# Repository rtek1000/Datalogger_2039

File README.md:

# Datalogger 2039
- This is an 8-channel logger for collecting temperature data (431 160 readings).
- - Data export via USB Flash Drive (Pendrive).
- - Digital sensor.
- Project started in Jan/2019.
- - Note: Work in progress, just demonstrative, not (fully) functional, sorry.
- - If you are using a browser on your smartphone, use the landscape screen to read more characters in the file names.
- - - (These files have already been cited elsewhere, and changing the name of the folders causes corruption of the references)

-------

## Features:
- 12-bit temperature sensor [DS18B20 from -55°C to +125°C (-67°F to +257°F)]
- - Needs two cycles to reset fault (Cycle 1: Start converting; Cycle 2: Read)
- 16-bit temperature sensor [TMP117 from -55°C to 150°C and from 0°C to 85°C for letter M code)]
- Short circuit protection for sensors (power and data line).
- Short-circuit protection for the USB ports (power line).
- 56 characters channel label.
- Special character supported for channel label (À/Á/Ã/Â/Ä).
- Channel label Ctrl+C/Ctrl+V (copy/paste) supported.
- 53 895 readings per channel (37 days, 10 hours and 15 minutes @ 1 minute interval).
- Control access to settings and data export via password.
- Export data via USB Flash Drive (Pendrive) (*.dat file).
- - Before removing the USB disk It is recommended to exit the Export screen to completely disable the USB port.
- - Need to format the USB disk in FAT (FAT32, LBA; exFAT may be faster), or it will give an error.
- - Output file with part of the data encoded in Base64. Need to decode the data to import into a spreadsheet, see the File Converter App.
- - Formatting USB flash drive on [Android](https://support-en.wd.com/app/answers/detailweb/a_id/40101/~/format-a-usb-drive-or-memory-card-using-android) did not cause error (tested on Motorola Smartphone and Android version 10).
- - Quick formatting may cause an error if the previous partition is not FAT, in this case use full formatting.
- USB Flash Drive (Pendrive) format function (Be careful, all files will be lost).
- - Some USB disks may not be recognized correctly on Android smartphones when using exFAT.
- Edit parameters via USB keyboard.
- - Keyboard may take a few seconds to recognize.
- - Support to [Wireless Mini Keyboard with Touchpad built in](https://github.com/rtek1000/Datalogger_2039/blob/main/Hardware/Wireless%20Mini%20Keyboard/Mini_Keyboard_Colors.jpg) ([Tested with PT-BR layout](https://github.com/rtek1000/Datalogger_2039/tree/main/Hardware/Wireless%20Mini%20Keyboard)).
- Cabinet tilt monitoring.
- Battery and charger voltage monitoring.
- Battery polarity reversal protection (In case the Datalogger 2039 is using two batteries, it is not recommended to reverse any of them, or it may damage the battery).
- Monitoring of data in colored graph.
- Can save Screenshot to USB flash drive (PrintScreen key).
- Multiple languages (English, Portuguese and Spanish).
- [Integrated firmware integrity check (CRC)](https://community.st.com/t5/security-mcu/how-to-use-hal-crc-accumulate-bufferlength-does-not-accept-the/td-p/252363).
- Energy saving for prolonged battery charge and durability of the LCD backlight.
- - Microcontroller operates in two modes, low power at only 40MHz clock and normal power at 168MHz clock.
- - The display is activated only when the microcontroller is clocked at 168MHz.
- - The display backlight has 3 operating states: high brightness, low brightness and off.
- - When the sensor is read, a conversion interval of 750ms is required (DS18B20), during which time the microcontroller sleeps.
- Temperature offset. On the sensors screen, press the number between 1 and 8 to open the offset adjustment screen.

## Software:
- Firmware for STM32F407VGT6 microcontroller:
- - STM32CubeIDE - C language project (HAL).
- File Converter:
- -  ̶B̶4̶J̶ ̶-̶ ̶B̶a̶s̶i̶c̶ ̶l̶a̶n̶g̶u̶a̶g̶e̶ ̶p̶r̶o̶j̶e̶c̶t̶ ̶(̶J̶a̶v̶a̶ ̶-̶ ̶c̶r̶o̶s̶s̶ ̶p̶l̶a̶t̶f̶o̶r̶m̶)̶.̶
- - Dot Net 4.0 - [SharpDevelop 4.4.1](https://sourceforge.net/projects/sharpdevelop/files/SharpDevelop%204.x/4.4/)

## Hardware:
- STM32F407VGT6: Dual USB port microcontroller.
- DS18B20: OneWire digital temperature sensor (±0.5°C Accuracy from -10°C to +85°C).
- TMP117: I2C digital temperature sensor (±0.1°C; 16 bits).
- TCA9548A: 8CH I2C Multiplexer.
- CD74HC595: Port expansion (8-Bit Serial-In, Parallel-Out Shift)
- ILI9341: SPI TFT LCD 2.4 inch.
- W25Q64: SPI flash memory (64M-bit).
- DS3231: I2C extremely accurate real time clock - RTC.
- - CR2032: Lithium 3.0V battery backup.
- MPU6050: I2C accelerometer (ACC).
- USBLC6-2: ESD protection.
- STMPS2141: Enhanced single channel power switch (500mA continuous current)
- 18650: Li-ion 3.7V battery backup.
- TP4056: Battery charger.
- MCP1700: 1.6 µA Quiescent Current (IQ) Linear voltage regulator.
- LMR14020: High efficiency 2.2 MHz 2A Step-Down Converter (40V, 40µA IQ).
- MT3608: High Efficiency 1.2MHz 2A Step Up Converter (Up to 28V)
- LAN8720: High-Performance 10/100 Ethernet (For future connectivity expansion).
- 12V DC charger (9V~24V x 2A)
- Multi-functional button:
- - For manual activation when in economy mode
- - To force restart of the USB port (keyboard)
- - To force restart the microcontroller

Note:
- Series resistor on the USB line must be removed (cables must be shorter than 5 meters) see video:
- - [STM32 USB training - 07 STM32 USB hardware design]
- - https://www.youtube.com/watch?v=vwlXUOY7KY0&list=PLnMKNibPkDnFFRBVD206EfnnHhQZI4Hxa&index=7

- Calibration?
- - https://thecavepearlproject.org/2016/03/05/ds18b20-calibration-we-finally-nailed-it/

Note: If the pins PA13 (SWDIO) and PA14 (SWCLK) are used (configured for another option other than the default state) it may prevent the ST-Link from working, to solve this problem, keep the BOOT0 (pin 94) in logical state high (3.3V) before energizing (reset the microcontroller). To not need to manually change the BOOT0 pin, keep the pins PA13 (SWDIO) and PA14 (SWCLK) unused, it also cannot be configured as input.

-------

#### ToDo
- Add factory reset (W25Q64 chip erase).
- Add offset adjustment lock if sensor is in use.
- Add a link to the offset value to the sensor serial number (user may need to reposition sensors).
- Add / Implement drivers for I2C and SPI peripherals using DMA.
- Modify USB Flash Drive port power to be enabled only when data export is confirmed.
-
- Note: Fixes and improvements noted in the [changelog.txt](https://github.com/rtek1000/Datalogger_2039/blob/main/Software/Datalogger_2039%20-%20STM32/BIN/Evaluation%20version/changelog.txt) file.
- - Annotations started from project update date using STM32CubeIDE version 1.12.1 ([FW_F4](https://www.st.com/en/embedded-software/stm32cubef4.html) 1.27.1).

### Downgrade firmware

Note: To go back to version 0.0.7 after installing firmware 0.0.8:
- Version 0.0.7 does not support the [Wireless Mini Keyboard with Touchpad built in](https://github.com/rtek1000/Datalogger_2039/tree/main/Hardware/Wireless%20Mini%20Keyboard).
- - User needs to use normal USB keyboard **without** built-in touchpad.
-
- Version 0.0.7 powers USB ports differently than version 0.0.8.
- - If the battery is disconnected or low charge, infinite loop may occur when booting.
- - On the serial port UART1 it is possible to see that an infinite initialization loop occurs (via [PuTTy](https://www.chiark.greenend.org.uk/~sgtatham/putty/latest.html) 115200 bauds).
- - Only the 5V regulator (U12) does not provide enough power to activate the DC-DC converter (U11) with the USB ports in use.
- - Without 5V from U11, the display cannot turn on.
- - The user can disconnect the keyboard (USB1) to verify that the problem stops occurring.
- - User needs to provide functional battery for normal operation.

-------

LCD Graph screen screenshot:

- [File conversion app](https://github.com/rtek1000/Datalogger_2039/tree/main/Software/Datalogger_2039%20-%20SharpDevelop) (*.exe) has been updated with partial language support

--------
## STM32 internal hardware USB:

- Regarding the hardware problem in the STM32, for new projects that can use a USB HUB in the USB port operating as a Host, it may be recommended to use an [external PHY](https://community.st.com/t5/stm32-mcu-products/is-it-possible-to-use-usb-hub-with-stm32f4-using-external-phy/m-p/569817/highlight/true#M217311): see the doc [Errata sheet - ES0206 - Rev 19 - February 2023](https://www.st.com/resource/en/errata_sheet/es0206-stm32f427437-and-stm32f429439-device-errata-stmicroelectronics.pdf).

Each model may have an ERRATA document, check on the ST website under the Documentation tab. Series of STM32 can have similar functions, as for example the [F4 and F7](https://community.st.com/t5/stm32-mcu-products/is-there-any-stm32-f7-or-h7-pin-compatible-with-stm32f407vgt6/m-p/568289/highlight/true#M216887) series:

--------

[Failures may occur in the USB port operating as a Host](https://community.st.com/t5/stm32-mcu-products/stm32-usb-host-fails-miserably-but-arduino-mega2560-and-uno-with/td-p/569199) if the connected device lacks synchronization (not very accurate time base, such as using a ceramic resonator instead of a quartz crystal). The same device (joypad) that failed with STM32, didn't fail with Arduino and MAX3421e, can be an interesting alternative, library: [UHS3.0](https://github.com/felis/UHS30)

- The image below shows data that the STM32 read from the device during the device recognition (enumeration) procedure, and subsequent readings are not the same.

(Test [code](https://github.com/rtek1000/STM32F4HUB_modified/blob/main/Project-STM32CubeIDE_USBH_ASC/F407_USBH_ASC_GAMEPAD/F407_USBH_ASC/Middlewares/ST/STM32_USB_Host_Library/Class/HID/Src/usbh_hid.c)):

```C++
#if PRINT_HID_REPORT_DESCRIPTOR == 1
			USBH_UsrLog("Dump HID Report Descriptor start");
			printf("wItemLength %d\n", HID_Handle->HID_Desc.wItemLength);

			for(uint16_t i = 0; i < HID_Handle->HID_Desc.wItemLength; i++){
				printf("0x%02X ", phost->device.Data[i]);
			}

			printf("\n");
			USBH_UsrLog("Dump HID Report Descriptor end");
#endif // #if PRINT_HID_REPORT_DESCRIPTOR == 1
```

- Ref.: [USB Descriptor and Request Parser](https://eleccelerator.com/usbdescreqparser/) 

- See too: ESP32-S3 has 1x USB Host port, and can recognize keyboard with touchpad, [Code and details](https://github.com/espressif/esp-idf/issues/12667#issuecomment-1827783341)

--------

## Licence:

#### Hardware:
Released under CERN OHL 1.2: https://ohwr.org/cernohl

#### Software:
This library is free software; you can redistribute it and/or modify it under the terms of the GNU Lesser General Public License as published by the Free Software Foundation; either version 2.1 of the License, or (at your option) any later version.

This library is distributed in the hope that it will be useful, but WITHOUT ANY WARRANTY; without even the implied warranty of MERCHANTABILITY or FITNESS FOR A PARTICULAR PURPOSE. See the GNU Lesser General Public License for more details.

You should have received a copy of the GNU Lesser General Public License along with this library; if not, write to the Free Software Foundation, Inc., 51 Franklin St, Fifth Floor, Boston, MA 02110-1301 USA

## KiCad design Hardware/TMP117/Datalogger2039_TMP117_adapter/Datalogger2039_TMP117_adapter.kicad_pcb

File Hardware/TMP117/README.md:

- Support for [TMP117](https://www.ti.com/product/TMP117) (+/-0.1°C; 16 bits) sensors (8CH using I2C Multiplexer IC [TCA9548A](https://www.sparkfun.com/products/16784) connected on the I2C3 data bus, connection [reference U17](https://github.com/rtek1000/Datalogger_2039/blob/main/Hardware/Datalogger_2039.pdf) (24AA02E48-I/SN not placed))
- - TMP117 high-accuracy temperature sensor
- - - ±0.1 °C (maximum) from –20 °C to +50 °C
- - - ±0.15 °C (maximum) from –40 °C to +70 °C
- - - ±0.2 °C (maximum) from –40 °C to +100 °C
- - - ±0.25 °C (maximum) from –55 °C to +125 °C
- - - ±0.3 °C (maximum) from –55 °C to +150 °C
- - - Operating temperature range: –55 °C to +150 °C (For model with letter M: 0°C to 85°C only)
- - Due to the high sensitivity of the sensor, manual soldering can affect the TMP117, it may be more advisable to buy assembled PCB boards, for example [Adafruit](https://www.adafruit.com/product/4821) and [SparkFun](https://www.sparkfun.com/products/15805) boards
- - - WSON package: [SON Temperature Profile](https://www.ti.com/lit/an/slua271b/slua271b.pdf)
- - - - Rework Guidelines: "Do not reuse the part after it is removed" (Pag 16, Table 3)
-
- - - DSBGA package: [BGA Temperature Profile](https://www.ti.com/lit/wp/ssyz015b/ssyz015b.pdf)
-
- - - SON package ([Infineon](https://www.infineon.com/dgdl/Infineon-Additional_product_information_SON_packages-AN-v00_01-EN.pdf?fileId=db3a30433e82b1cf013e82faab2000e5)): "Due to possible damage while removing the component, a desoldered component
should not be reused"
-
- - Maybe the 138°C soldering (Sn/Bi) could be used to prevent damage to the sensor and perhaps allow reuse after the sensor is removed from the board (possibly applicable for model with letter M, TMP117M, working temperature 0°C to 85°C only).
 
- TMP117 Custom Board:

- TMP117 Custom Board schematic:

- Interface adapter:

- Interface schematic:

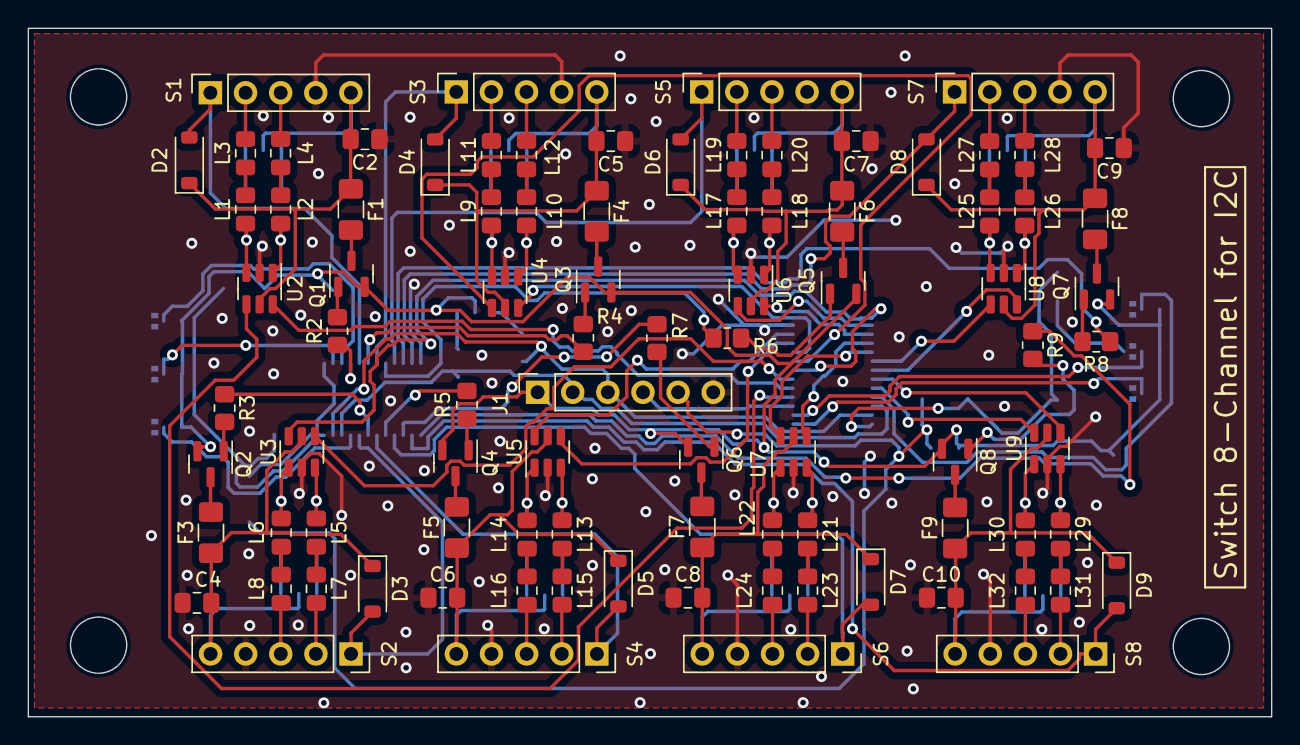
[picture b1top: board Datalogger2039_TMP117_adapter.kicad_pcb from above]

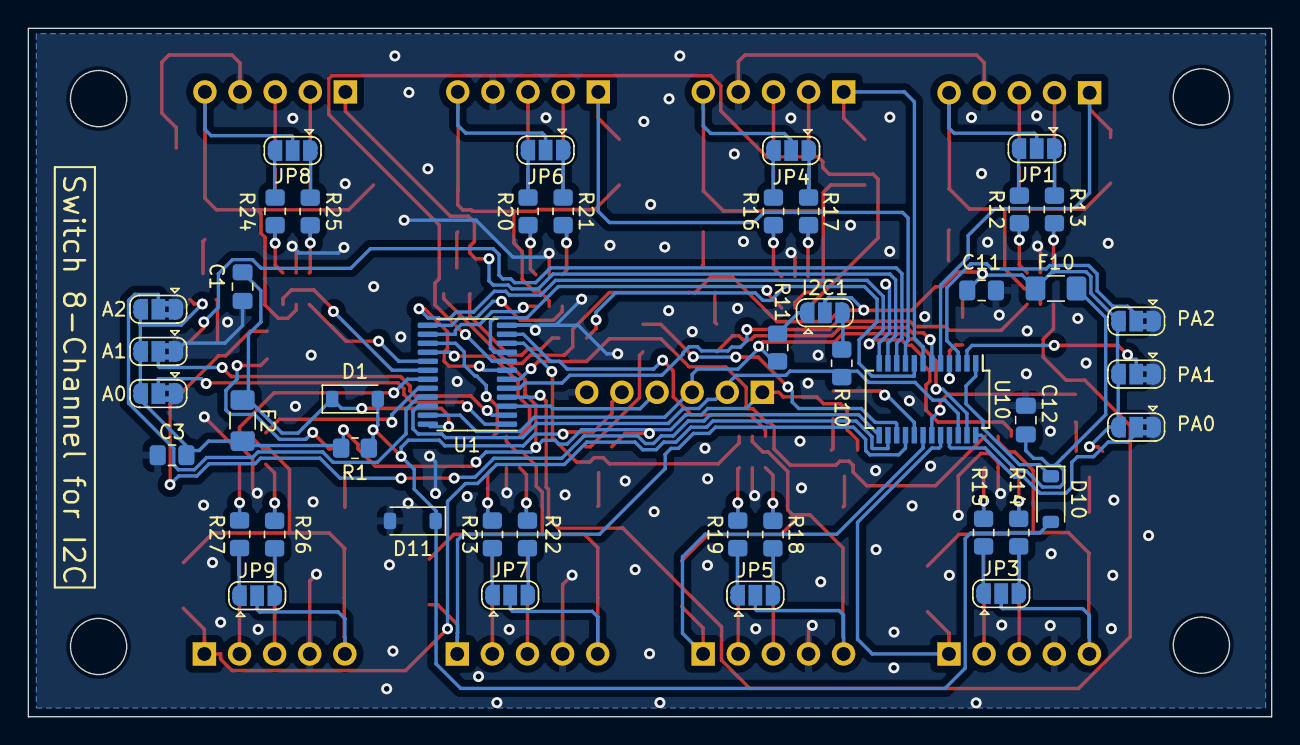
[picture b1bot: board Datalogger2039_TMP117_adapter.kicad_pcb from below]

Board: 2 copper layers, 89.9 x 49.8 mm, 134 parts (45 on the bottom side), 137 nets.

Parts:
A0: A0; SolderJumper-3_P1.3mm_Bridged2Bar12_RoundedPad1.0x1.5mm
A1: A1; SolderJumper-3_P1.3mm_Bridged2Bar12_RoundedPad1.0x1.5mm
A2: A2; SolderJumper-3_P1.3mm_Bridged2Bar12_RoundedPad1.0x1.5mm
C1, C2, C3, C4, C5, C6, C7, C8, C9, C10, C11, C12: 100n; C_0805_2012Metric_Pad1.18x1.45mm_HandSolder
D1, D2, D3, D4, D5, D6, D7, D8, D9, D10: 1N4148W; D_SOD-123
D11: 5V1; D_SOD-123
F1, F3, F4, F5, F6, F7, F8, F9: 1206L005 60WR; Fuse_1206_3216Metric_Pad1.42x1.75mm_HandSolder
F2, F10: 1206L025YR; Fuse_1206_3216Metric_Pad1.42x1.75mm_HandSolder
I2C1: SolderJumper_3_Open; SolderJumper-3_P1.3mm_Open_RoundedPad1.0x1.5mm
J1: To_MCU; PinSocket_1x06_P2.54mm_Vertical
JP1, JP3, JP4, JP5, JP6, JP7, JP8, JP9: SolderJumper_3_Open; SolderJumper-3_P1.3mm_Open_RoundedPad1.0x1.5mm
L1, L2, L3, L4, L5, L6, L7, L8, L9, L10, L11, L12, L13, L14, L15, L16, L17, L18, L19, L20, L21, L22, L23, L24, L25, L26, L27, L28, L29, L30, L31, L32: PBY201209T-102Y-N; L_0805_2012Metric_Pad1.15x1.40mm_HandSolder
PA0, PA1, PA2: A0; SolderJumper-3_P1.3mm_Bridged2Bar12_RoundedPad1.0x1.5mm
Q1, Q2, Q3, Q4, Q5, Q6, Q7, Q8: AO3401A; SOT-23
R1, R2, R3, R4, R5, R6, R7, R8, R9: 10k; R_0805_2012Metric_Pad1.20x1.40mm_HandSolder
R10, R11, R12, R13, R14, R15, R16, R17, R18, R19, R20, R21, R22, R23, R24, R25, R26, R27: 4k7; R_0805_2012Metric_Pad1.20x1.40mm_HandSolder
S1, S2, S3, S4, S5, S6, S7, S8: To_TMP117; PinSocket_1x05_P2.54mm_Vertical
U1: TCA9548APWR; TSSOP-24_4.4x7.8mm_P0.65mm
U2, U3, U4, U5, U6, U7, U8, U9: USBLC6-2SC6; SOT-23-6
U10: PCF8575MS/TR; SSOP-24_3.9x8.7mm_P0.635mm

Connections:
Alert: D1.2 (A), D10.2 (A), D11.1 (K), J1.5, R1.2
Alert0: D2.2 (A), S1.1, U10.5 (P01)
Alert1: D3.2 (A), S2.1, U10.20 (P17)
Alert2: D4.2 (A), S3.1, U10.7 (P03)
Alert3: D5.2 (A), S4.1, U10.18 (P15)
Alert4: D6.2 (A), S5.1, U10.9 (P05)
Alert5: D7.2 (A), S6.1, U10.16 (P13)
Alert6: D8.2 (A), S7.1, U10.11 (P07)
Alert7: D9.2 (A), S8.1, U10.14 (P11)
GND: A0.1 (A), A1.1 (A), A2.1 (A), C1.1, C2.1, C3.1, C4.1, C5.1, C6.1, C7.1, C8.1, C9.1, C10.1, C11.1, C12.1, D11.2 (A), J1.6, PA0.1 (A), PA1.1 (A), PA2.1 (A), S1.4, S2.4, S3.4, S4.4, S5.4, S6.4, S7.4, S8.4, U1.12 (GND), U2.2 (GND), U3.2 (GND), U4.2 (GND), U5.2 (GND), U6.2 (GND), U7.2 (GND), U8.2 (GND), U9.2 (GND), U10.12 (GND)
unnamed: A0.2 (C), U1.1 (A0)
unnamed: A1.2 (C), U1.2 (A1)
unnamed: A2.2 (C), U1.21 (A2)
unnamed: C1.2, D1.1 (K), F2.1, U1.24 (VCC)
unnamed: C2.2, D2.1 (K), F1.1, JP1.2 (C), S1.5, U2.5 (VBUS)
unnamed: C4.2, D3.1 (K), F3.1, JP3.2 (C), S2.5, U3.5 (VBUS)
unnamed: C5.2, D4.1 (K), F4.1, JP4.2 (C), S3.5, U4.5 (VBUS)
unnamed: C6.2, D5.1 (K), F5.1, JP5.2 (C), S4.5, U5.5 (VBUS)
unnamed: C7.2, D6.1 (K), F6.1, JP6.2 (C), S5.5, U6.5 (VBUS)
unnamed: C8.2, D7.1 (K), F7.1, JP7.2 (C), S6.5, U7.5 (VBUS)
unnamed: C9.2, D8.1 (K), F8.1, JP8.2 (C), S7.5, U8.5 (VBUS)
unnamed: C10.2, D9.1 (K), F9.1, JP9.2 (C), S8.5, U9.5 (VBUS)
unnamed: D10.1 (K), U10.1 (*INT)
unnamed: I2C1.1 (A), R11.2
unnamed: I2C1.3 (B), R10.2
unnamed: J1.4, U1.3 (~RESET)
unnamed: JP1.1 (A), R13.2
unnamed: JP1.3 (B), R12.2
unnamed: JP3.1 (A), R15.2
unnamed: JP3.3 (B), R14.2
unnamed: JP4.1 (A), R17.2
unnamed: JP4.3 (B), R16.2
unnamed: JP5.1 (A), R19.2
unnamed: JP5.3 (B), R18.2
unnamed: JP6.1 (A), R21.2
unnamed: JP6.3 (B), R20.2
unnamed: JP7.1 (A), R23.2
unnamed: JP7.3 (B), R22.2
unnamed: JP8.1 (A), R25.2
unnamed: JP8.3 (B), R24.2
unnamed: JP9.1 (A), R27.2
unnamed: JP9.3 (B), R26.2
unnamed: L1.1, R13.1, U2.3 (I/O2)
unnamed: L1.2, L3.1
unnamed: L2.1, R12.1, U2.1 (I/O1)
unnamed: L2.2, L4.1
unnamed: L5.1, R15.1, U3.3 (I/O2)
unnamed: L5.2, L7.1
unnamed: L6.1, R14.1, U3.1 (I/O1)
unnamed: L6.2, L8.1
unnamed: L9.1, R17.1, U4.3 (I/O2)
unnamed: L10.1, R16.1, U4.1 (I/O1)
unnamed: L10.2, L12.1
unnamed: L9.2, L11.1
unnamed: L13.1, R19.1, U5.3 (I/O2)
unnamed: L13.2, L15.1
unnamed: L14.1, R18.1, U5.1 (I/O1)
unnamed: L14.2, L16.1
unnamed: L17.1, R21.1, U6.3 (I/O2)
unnamed: L17.2, L19.1
unnamed: L18.1, R20.1, U6.1 (I/O1)
unnamed: L18.2, L20.1
unnamed: L21.1, R23.1, U7.3 (I/O2)
unnamed: L21.2, L23.1
unnamed: L22.1, R22.1, U7.1 (I/O1)
unnamed: L22.2, L24.1
unnamed: L25.1, R25.1, U8.3 (I/O2)
unnamed: L25.2, L27.1
unnamed: L26.1, R24.1, U8.1 (I/O1)
unnamed: L26.2, L28.1
unnamed: L29.1, R27.1, U9.3 (I/O2)
unnamed: L29.2, L31.1
unnamed: L30.1, R26.1, U9.1 (I/O1)
unnamed: L30.2, L32.1
unnamed: PA0.2 (C), U10.21 (A0)
unnamed: PA1.2 (C), U10.2 (A1)
unnamed: PA2.2 (C), U10.3 (A2)
unnamed: F1.2, Q1.3 (D)
unnamed: Q1.1 (G), R2.2
unnamed: F3.2, Q2.3 (D)
unnamed: Q2.1 (G), R3.2
unnamed: F4.2, Q3.3 (D)
unnamed: Q3.1 (G), R4.2
unnamed: F5.2, Q4.3 (D)
unnamed: Q4.1 (G), R5.2
unnamed: F6.2, Q5.3 (D)
unnamed: Q5.1 (G), R6.2
unnamed: F7.2, Q6.3 (D)
unnamed: Q6.1 (G), R7.2
unnamed: F8.2, Q7.3 (D)
unnamed: Q7.1 (G), R8.2
unnamed: F9.2, Q8.3 (D)
unnamed: Q8.1 (G), R9.2
unnamed: L3.2, S1.2
unnamed: L4.2, S1.3
unnamed: L7.2, S2.2
unnamed: L8.2, S2.3
unnamed: L11.2, S3.2
unnamed: L12.2, S3.3
unnamed: L15.2, S4.2
unnamed: L16.2, S4.3
unnamed: L19.2, S5.2
unnamed: L20.2, S5.3
unnamed: L23.2, S6.2
unnamed: L24.2, S6.3
unnamed: L27.2, S7.2
unnamed: L28.2, S7.3
unnamed: L31.2, S8.2
unnamed: L32.2, S8.3
unnamed: C12.2, F10.1, U10.24 (VCC)
Power0: R2.1, U10.4 (P00)
Power1: R3.1, U10.19 (P16)
Power2: R4.1, U10.6 (P02)
Power3: R5.1, U10.17 (P14)
Power4: R6.1, U10.8 (P04)
Power5: R7.1, U10.15 (P12)
Power6: R8.1, U10.10 (P06)
Power7: R9.1, U10.13 (P10)
SCL: J1.2, R10.1, U1.22 (SCL), U10.22 (SCL)
SCL0: U1.5 (SC0), U2.6 (I/O1)
SCL1: U1.7 (SC1), U3.6 (I/O1)
SCL2: U1.9 (SC2), U4.6 (I/O1)
SCL3: U1.11 (SC3), U5.6 (I/O1)
SCL4: U1.14 (SC4), U6.6 (I/O1)
SCL5: U1.16 (SC5), U7.6 (I/O1)
SCL6: U1.18 (SC6), U8.6 (I/O1)
SCL7: U1.20 (SC7), U9.6 (I/O1)
SDA: J1.3, R11.1, U1.23 (SDA), U10.23 (SDA)
SDA0: U1.4 (SD0), U2.4 (I/O2)
SDA1: U1.6 (SD1), U3.4 (I/O2)
SDA2: U1.8 (SD2), U4.4 (I/O2)
SDA3: U1.10 (SD3), U5.4 (I/O2)
SDA4: U1.13 (SD4), U6.4 (I/O2)
SDA5: U1.15 (SD5), U7.4 (I/O2)
SDA6: U1.17 (SD6), U8.4 (I/O2)
SDA7: U1.19 (SD7), U9.4 (I/O2)
VCC: A0.3 (B), A1.3 (B), A2.3 (B), C3.2, C11.2, F2.2, F10.2, I2C1.2 (C), J1.1, PA0.3 (B), PA1.3 (B), PA2.3 (B), Q1.2 (S), Q2.2 (S), Q3.2 (S), Q4.2 (S), Q5.2 (S), Q6.2 (S), Q7.2 (S), Q8.2 (S), R1.1

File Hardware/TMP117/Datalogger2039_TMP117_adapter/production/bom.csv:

Designator,Footprint,Quantity,Value,LCSC Part #
"C1, C10, C11, C12, C2, C3, C4, C5, C6, C7, C8, C9",0805,12,100n,C2930278
"D1, D10, D2, D3, D4, D5, D6, D7, D8, D9",D_SOD-123,10,1N4148W,C917030
D11,D_SOD-123,1,5V1,
"F1, F3, F4, F5, F6, F7, F8, F9",1206,8,1206L005 60WR,C315892
"F10, F2",1206,2,1206L025YR,C99561
J1,PinSocket_1x06_P2.54mm_Vertical,1,To_MCU,C2685156
"L1, L10, L11, L12, L13, L14, L15, L16, L17, L18, L19, L2, L20, L21, L22, L23, L24, L25, L26, L27, L28, L29, L3, L30, L31, L32, L4, L5, L6, L7, L8, L9",0805,32,PBY201209T-102Y-N ,C142064
"Q1, Q2, Q3, Q4, Q5, Q6, Q7, Q8",SOT-23,8,AO3401A,
"R1, R2, R3, R4, R5, R6, R7, R8, R9",0805,9,10k,C2930231
"R10, R11, R12, R13, R14, R15, R16, R17, R18, R19, R20, R21, R22, R23, R24, R25, R26, R27",0805,18,4k7,C2930231
"S1, S2, S3, S4, S5, S6, S7, S8",PinSocket_1x05_P2.54mm_Vertical,8,To_TMP117,C2935904
U1,TSSOP-24_4.4x7.8mm_P0.65mm,1,TCA9548APWR,C130026
U10,SSOP-24_3.9x8.7mm_P0.635mm,1,PCF8575MS/TR,
"U2, U3, U4, U5, U6, U7, U8, U9",SOT-23-6,8,USBLC6-2SC6,C2687116

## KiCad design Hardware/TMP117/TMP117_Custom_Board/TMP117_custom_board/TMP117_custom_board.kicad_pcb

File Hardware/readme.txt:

Note:
- For new projects with USB Host and certain models of STM32 it may be recommended to use an external PHY:

https://community.st.com/t5/stm32-mcu-products/is-it-possible-to-use-usb-hub-with-stm32f4-using-external-phy/m-p/569817/highlight/true#M217311

https://community.st.com/t5/embedded-software-mcus/stm32f429-discovery-as-usb-host-problems-enumerating-low-speed/m-p/306947/highlight/true#M21564

---------

####ISO 639-1 standard language codes

Language (Region)	- Code
Afrikaans - af
Albanian - sq
Arabic (Algeria) - ar-dz
Arabic (Bahrain) - ar-bh
Arabic (Egypt) - ar-eg
Arabic (Iraq) - ar-iq
Arabic (Jordan) - ar-jo
Arabic (Kuwait) - ar-kw
Arabic (Lebanon) - ar-lb
Arabic (Libya) - ar-ly
Arabic (Morocco) - ar-ma
Arabic (Oman) - ar-om
Arabic (Qatar) - ar-qa
Arabic (Saudi Arabia) - ar-sa
Arabic (Syria) - ar-sy
Arabic (Tunisia) - ar-tn
Arabic (U.A.E.) - ar-ae
Arabic (Yemen) - ar-ye
Basque - eu
Belarusian - be
Bulgarian - bg
Catalan - ca
Chinese (Hong Kong) - zh-hk
Chinese (PRC) - zh-cn
Chinese (Singapore) - zh-sg
Chinese (Taiwan) - zh-tw
Croatian - hr
Czech - cs
Danish - da
Dutch (Belgium) - nl-be
Dutch (Standard) - nl
English - en
English (Australia) - en-au
English (Belize) - en-bz
English (Canada) - en-ca
English (Ireland) - en-ie
English (Jamaica) - en-jm
English (New Zealand) - en-nz
English (South Africa) - en-za
English (Trinidad) - en-tt
English (United Kingdom) - en-gb
English (United States) - en-us
Estonian - et
Faeroese - fo
Farsi - fa
Finnish - fi
French (Belgium) - fr-be
French (Canada) - fr-ca
French (Luxembourg) - fr-lu
French (Standard) - fr
French (Switzerland) - fr-ch
Gaelic (Scotland) - gd
German (Austria) - de-at
German (Liechtenstein) - de-li
German (Luxembourg) - de-lu
German (Standard) - de
German (Switzerland) - de-ch
Greek - el
Hebrew - he
Hindi - hi
Hungarian - hu
Icelandic - is
Indonesian - id
Irish - ga
Italian (Standard) - it
Italian (Switzerland) - it-ch
Japanese - ja
Korean - ko
Korean (Johab) - ko
Kurdish - ku
Latvian - lv
Lithuanian - lt
Macedonian (FYROM) - mk
Malayalam - ml
Malaysian - ms
Maltese - mt
Norwegian - no
Norwegian (Bokmål) - nb
Norwegian (Nynorsk) - nn
Polish - pl
Portuguese (Brazil) - pt-br
Portuguese (Portugal) - pt
Punjabi - pa
Rhaeto-Romanic - rm
Romanian - ro
Romanian (Republic of Moldova) - ro-md
Russian - ru
Russian (Republic of Moldova) - ru-md
Serbian - sr
Slovak - sk
Slovenian - sl
Sorbian - sb
Spanish (Argentina) - es-ar
Spanish (Bolivia) - es-bo
Spanish (Chile) - es-cl
Spanish (Colombia) - es-co
Spanish (Costa Rica) - es-cr
Spanish (Dominican Republic) - es-do
Spanish (Ecuador) - es-ec
Spanish (El Salvador) - es-sv
Spanish (Guatemala) - es-gt
Spanish (Honduras) - es-hn
Spanish (Mexico) - es-mx
Spanish (Nicaragua) - es-ni
Spanish (Panama) - es-pa
Spanish (Paraguay) - es-py
Spanish (Peru) - es-pe
Spanish (Puerto Rico) - es-pr
Spanish (Spain) - es
Spanish (Uruguay) - es-uy
Spanish (Venezuela) - es-ve
Swedish - sv
Swedish (Finland) - sv-fi
Thai - th
Tsonga - ts
Tswana - tn
Turkish - tr
Ukrainian - ua
Urdu - ur
Venda - ve
Vietnamese - vi
Welsh - cy
Xhosa - xh
Yiddish - ji
Zulu - zu

Source: https://www.andiamo.co.uk/resources/iso-language-codes/

---------

Note:
- Editing software: KiCad E.D.A. Version: 5.1.6 [https://www.kicad.org/]

Note: Apparently there were no problems when opening the project with Kicad v6, only the first time it failed, in the following it opened the schema correctly.

Hardware Licence:
Released under CERN OHL 1.2: https://ohwr.org/cernohl

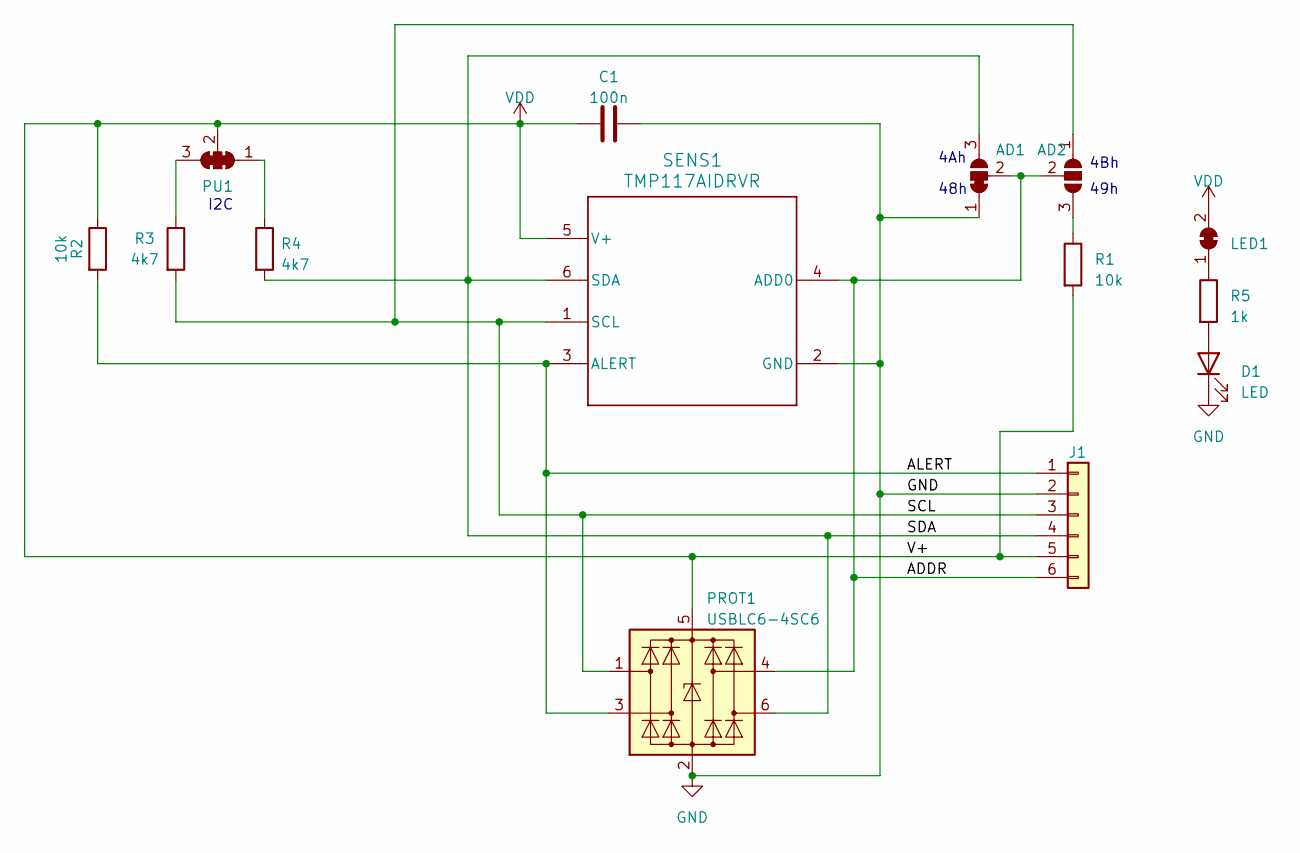
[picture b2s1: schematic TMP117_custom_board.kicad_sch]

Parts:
AD1: SolderJumper_3_Bridged12; SolderJumper-3_P1.3mm_Bridged12_RoundedPad1.0x1.5mm
AD2: SolderJumper_3_Open; SolderJumper-3_P1.3mm_Open_RoundedPad1.0x1.5mm
C1: 100n; C_0402_1005Metric_Pad0.74x0.62mm_HandSolder; LCSC Part C387941
D1: LED; LED_0603_1608Metric_Pad1.05x0.95mm_HandSolder; LCSC Part C2837379
J1: Conn_01x06; PinHeader_1x06_P2.54mm_Vertical
LED1: SolderJumper_2_Bridged; SolderJumper-2_P1.3mm_Bridged_RoundedPad1.0x1.5mm
PROT1: USBLC6-4SC6; SOT-23-6; LCSC Part C111212
PU1: SolderJumper_3_Bridged123; SolderJumper-3_P1.3mm_Bridged123_RoundedPad1.0x1.5mm
R1, R2: 10k; R_0603_1608Metric_Pad0.98x0.95mm_HandSolder; LCSC Part C116677
R3, R4: 4k7; R_0603_1608Metric_Pad0.98x0.95mm_HandSolder; LCSC Part C3016318
R5: 1k; R_0603_1608Metric_Pad0.98x0.95mm_HandSolder; LCSC Part C3016283
SENS1: TMP117AIDRVR; DRV0006B2; LCSC Part C699536

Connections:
/ADDR: AD1.2 (C), AD2.2 (C), J1.6, PROT1.4 (I/O3), SENS1.4 (ADD0)
/ALERT: J1.1, PROT1.3 (I/O2), R2.2, SENS1.3 (ALERT)
/SCL: AD2.1 (A), J1.3, PROT1.1 (I/O1), R3.2, SENS1.1 (SCL)
/SDA: AD1.3 (B), J1.4, PROT1.6 (I/O4), R4.2, SENS1.6 (SDA)
GND: AD1.1 (A), C1.2, D1.1 (K), J1.2, PROT1.2 (GND), SENS1.2 (GND)
unnamed: AD2.3 (B), R1.1
unnamed: D1.2 (A), R5.2
unnamed: LED1.1 (A), R5.1
unnamed: PU1.1 (A), R4.1
unnamed: PU1.3 (B), R3.1
VDD: C1.1, J1.5, LED1.2 (B), PROT1.5 (VBUS), PU1.2 (C), R1.2, R2.1, SENS1.5 (V+)

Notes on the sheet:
I2C
48h
4Bh
4Ah
49h

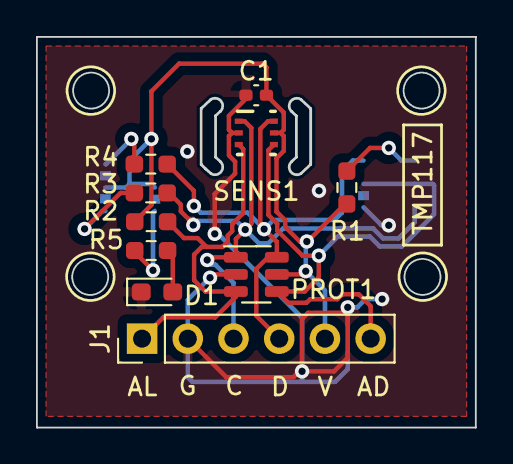
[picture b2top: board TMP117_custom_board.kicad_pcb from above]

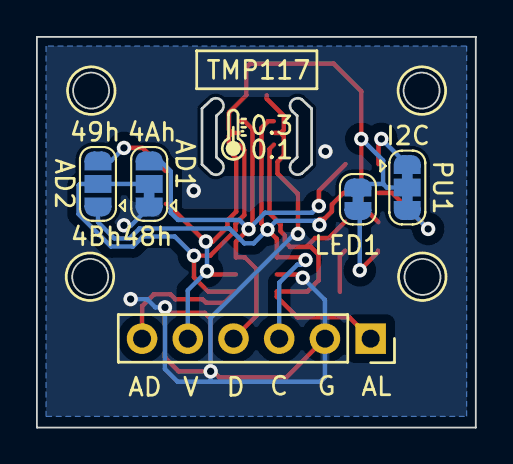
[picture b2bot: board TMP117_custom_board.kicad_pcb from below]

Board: 2 copper layers, 24.3 x 21.7 mm, 14 parts (4 on the bottom side), 11 nets.

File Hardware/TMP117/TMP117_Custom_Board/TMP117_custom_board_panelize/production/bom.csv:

Designator,Footprint,Quantity,Value,LCSC Part #
"C1_4, C1_3, C1_2, C1",0402,4,100n,C387941
"D1_4, D1_3, D1_2, D1",0603,4,LED,C2837379
"PROT1_4, PROT1_3, PROT1_2, PROT1",SOT-23-6,4,USBLC6-4SC6,C111212
"R1_4, R1_3, R1_2, R1, R2_4, R2_3, R2_2, R2",0603,8,10k,C116677
"R3_4, R3_3, R3_2, R3, R4_4, R4_3, R4_2, R4",0603,8,4k7,C3016318
"R5_4, R5_3, R5_2, R5",0603,4,1k,C3016283
"SENS1_4, SENS1_3, SENS1_2, SENS1",DRV0006B2,4,TMP117AIDRVR,C699536

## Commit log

2021-12-17 Software Update
2021-12-21 Software and Hardware Update
2022-01-04 Hardware & Software Update
2022-01-04 Hardware Update
2022-01-08 Software Update
    STM32CubeIDE_1.8.0
2022-01-09 Software Update
    Burn Flash with St-Link and Android
2022-01-16 Software Update
    Added Over Current Interrupt for USB Port (and DC-DC monitor)
2022-01-16 Software Update
    Error beep correction
2022-01-16 Software Update
    Log reduction
2022-02-12 Software Update
    LCD Backlight flashing, PWM frequency changed from ~300Hz to ~82kHz
2022-03-08 Update README.md
    Added calibration info
2022-03-08 Update README.md
    Update
2022-04-11 Update
    B4J App - Date Bug
2022-04-22 Software update
    B4J Application: Added *.csv file option
2022-05-06 Software update
    - Screenshot image file header was incorrect
    - Force disable USB flash drive after screenshot
2022-05-06 Added Usage.txt
    Basic description of use
2022-05-06 Usage.txt update
2022-05-10 Folder name correction
2022-05-10 Added SharpDevelop App
    Alternative software to App B4J, smaller executable.
2022-05-12 Delete Datalogger_2039_File_Converter.zip
    Update
2022-05-12 Create foo
2022-05-12 Update licence
2022-05-12 Create file
2022-05-16 Software Update
    Added software with RTOS
2022-05-16 Added licence file
2022-05-20 RTOS Software backup
2022-05-23 Add file
2022-05-23 Update file
2022-05-23 Update file name
2022-05-23 File name update
2022-05-26 File backup
    Programs using bootloader
2022-12-17 Software update
    Password screen
2022-12-26 Software update
    USB FS PWR bug found
2023-06-26 Update
    beep reactivated
2023-06-27 LCD driver update
    Modify the way to fill the screen
2023-06-27 Update
    Added timeout to skip 60 second refresh if keyboard is used
2023-06-27 Update
    Added flag for LCD timeout update (every minute)
2023-06-30 Update
    Fixes and improvements
2023-06-30 Update
    Added CRC failure warning
2023-07-09 Update
    Boards for TMP117 support
2023-07-10 Update
    BMP screenshots were converted to JPG to reduce repository space consumption
2023-07-10 Update
    Update screenshot images file name
2023-07-10 Update
    Screenshot filename update
2023-07-10 Update
    Screenshot images converted from BMP to PNG
2023-07-19 Rename readme.txt to readme.md
2023-07-24 Update
    Added preliminary option for TMP117 sensor selection
2023-08-16 Update
    TMP117 support
2023-08-16 Update
    TMP117 added
2023-08-16 Update
    Some bug fixes in the file converter
2023-11-01 Update
    Batt volt bug fix/modification
2023-11-12 Update
    IWDG bug fix
2023-11-13 Update
    Bug fix, incorrect sensor temperature unit (*C/*F)
2025-08-22 Update
    The board was panelized. JLCPCB increased the price of the board without panelization by 9x.
2025-08-22 Update
    Backup of KiKit panelizer settings (json)
2025-08-22 Update
    Small holes (0.15mm) have been enlarged to (0.25)
